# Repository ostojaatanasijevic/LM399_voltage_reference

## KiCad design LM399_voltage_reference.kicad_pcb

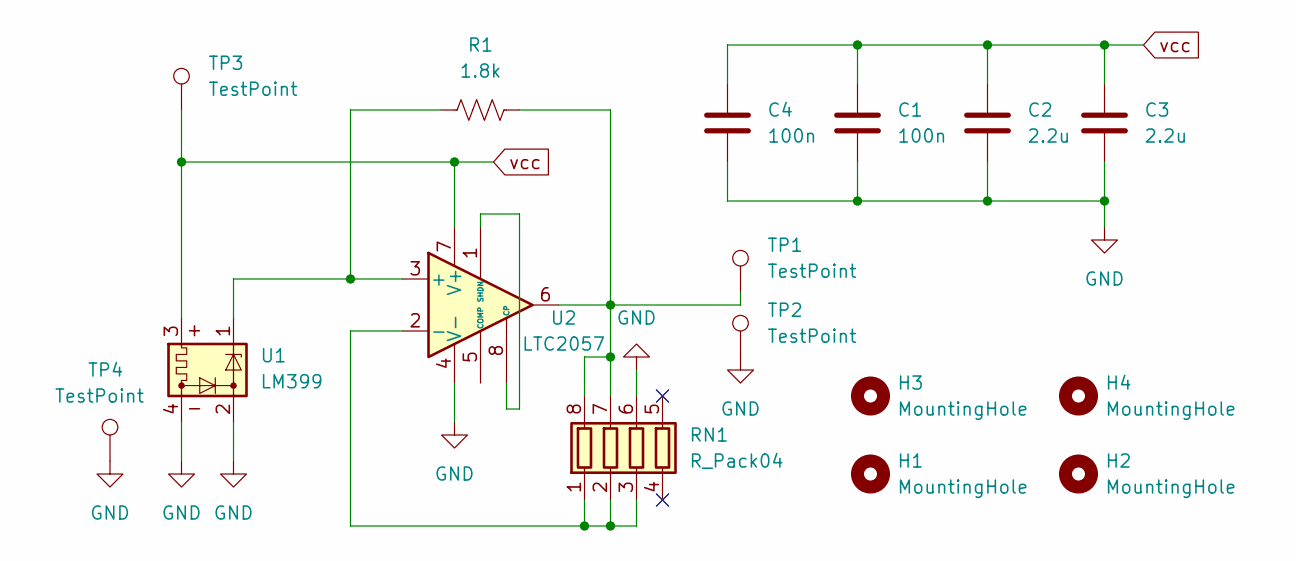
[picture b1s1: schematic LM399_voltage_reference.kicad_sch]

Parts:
C1, C4: 100n; C_0603_1608Metric_Pad1.08x0.95mm_HandSolder
C2, C3: 2.2u; C_0805_2012Metric_Pad1.18x1.45mm_HandSolder
H1, H2, H3, H4: MountingHole; MountingHole_3.2mm_M3
R1: 1.8k; R_0603_1608Metric_Pad0.98x0.95mm_HandSolder
RN1: R_Pack04; R_Array_Convex_4x0603
TP1, TP2, TP3, TP4: TestPoint; TestPoint_Pad_D4.0mm
U1: LM399; Analog_TO-46-4_ThermalShield
U2: LTC2057; SOIC-8_3.9x4.9mm_P1.27mm

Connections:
GND: C1.2, C2.2, C3.2, C4.2, RN1.6 (R3.2), TP2.1, TP4.1, U1.2, U1.4, U2.4 (V-)
unnamed: RN1.1 (R1.1), RN1.2 (R2.1), RN1.3 (R3.1), U2.2 (-)
unnamed: R1.2, RN1.7 (R2.2), RN1.8 (R1.2), TP1.1, U2.6
unnamed: R1.1, U1.1, U2.3 (+)
unnamed: U2.1 (SHDN), U2.8 (CP)
vcc: C1.1, C2.1, C3.1, C4.1, TP3.1, U1.3, U2.7 (V+)

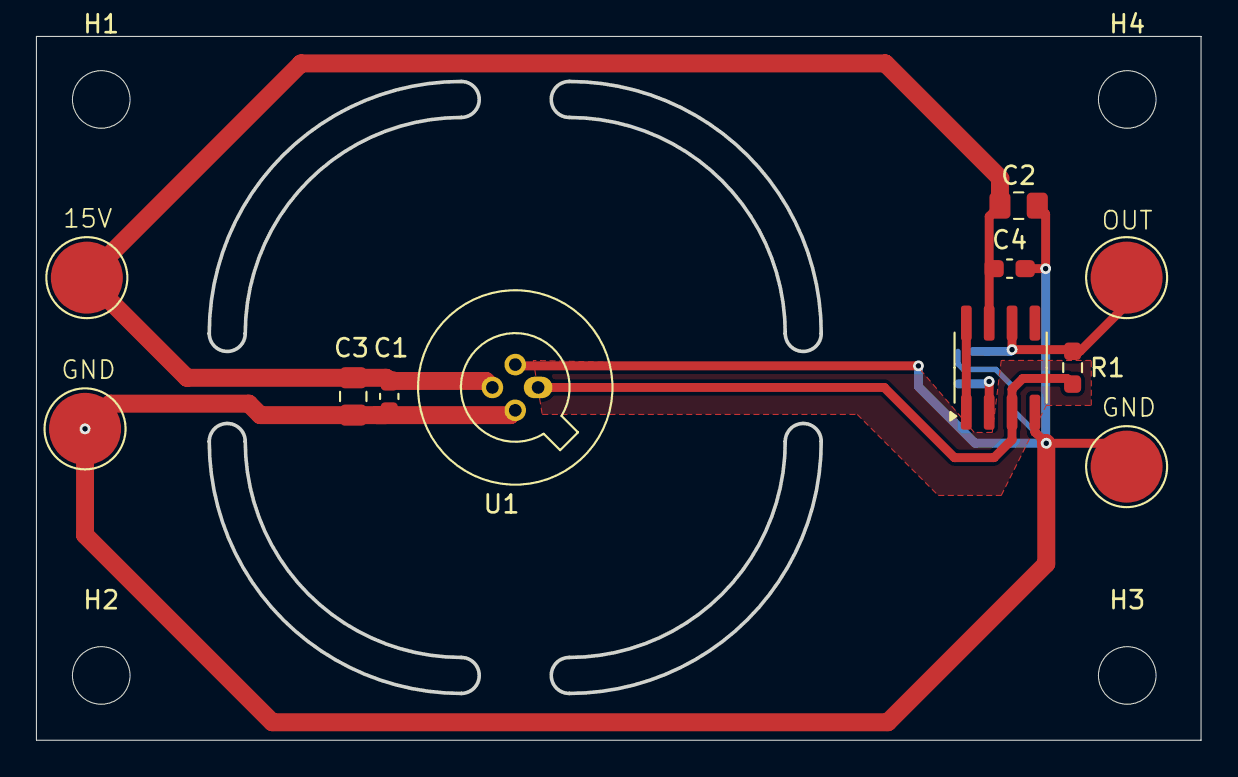
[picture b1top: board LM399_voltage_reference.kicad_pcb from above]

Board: 2 copper layers, 64.6 x 39.0 mm, 16 parts (1 on the bottom side), 6 nets.

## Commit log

2024-12-28 Init
2024-12-28 Nearly there.
2024-12-28 Done?
